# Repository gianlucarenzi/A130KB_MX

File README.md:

# A130KB_MX
ATARI XE Replacement Keyboard

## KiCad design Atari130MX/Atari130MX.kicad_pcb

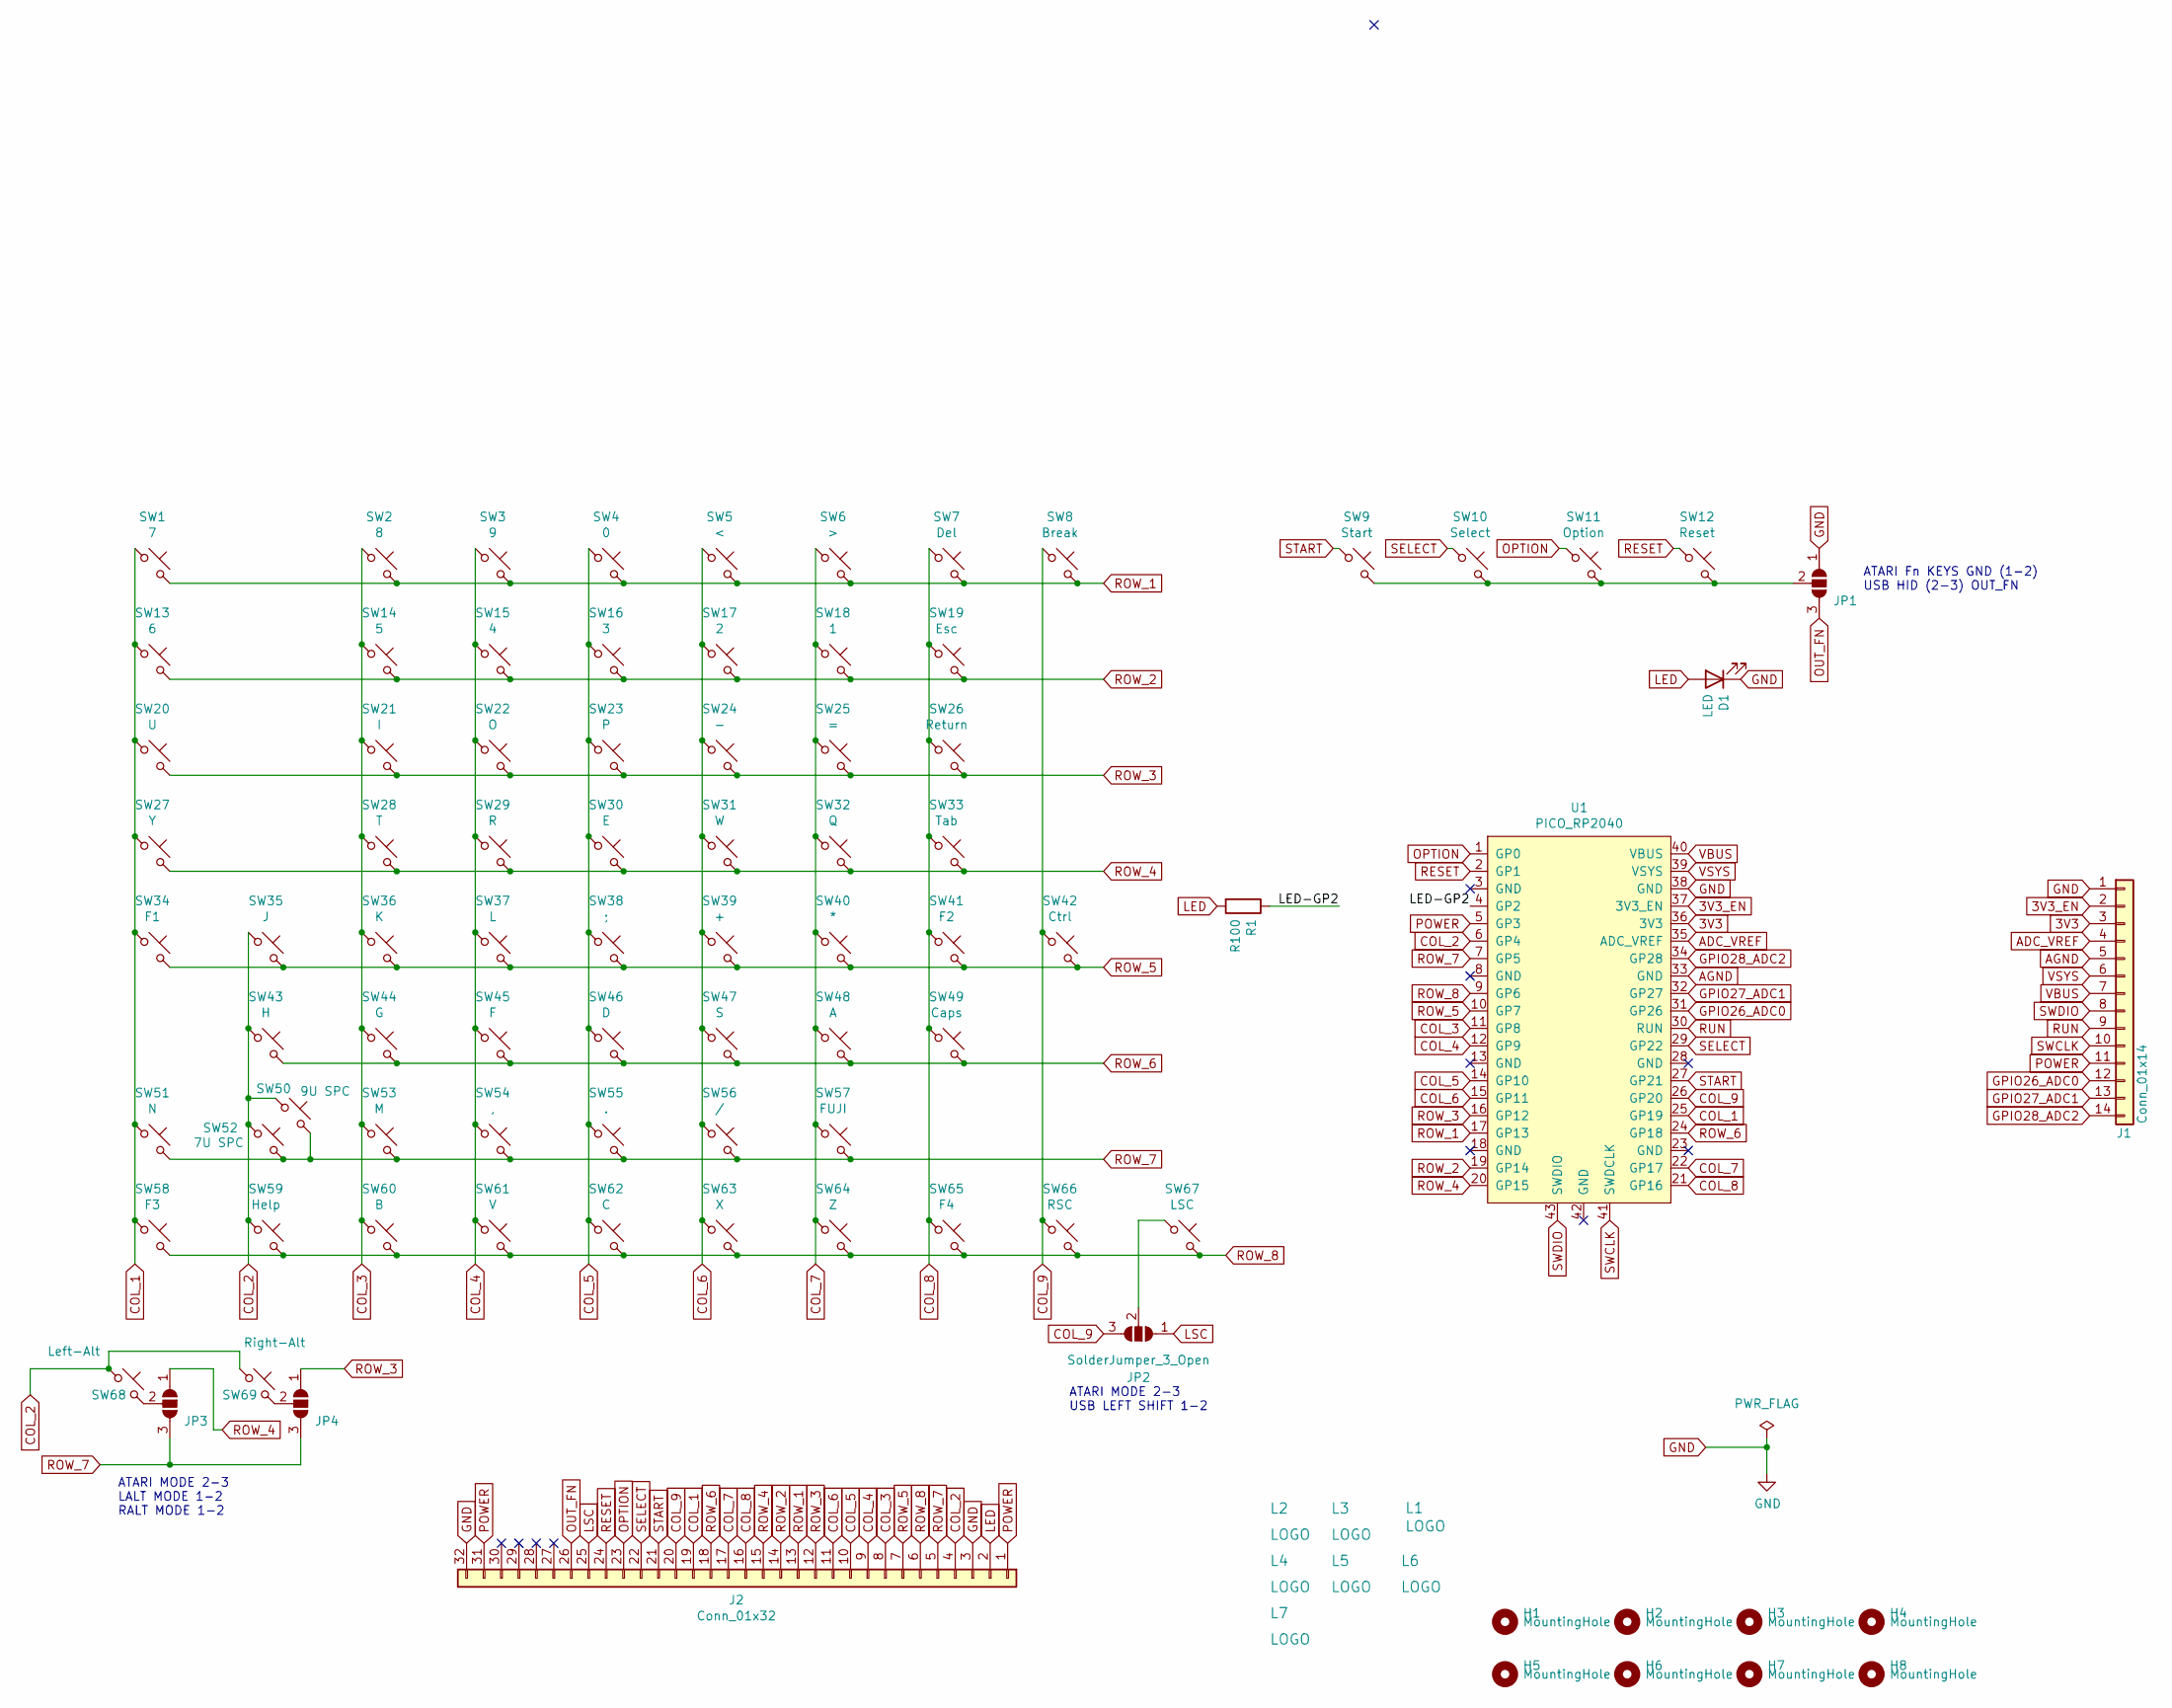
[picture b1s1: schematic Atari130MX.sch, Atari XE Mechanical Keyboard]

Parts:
D1: LED; LED_D3.0mm_Horizontal_O1.27mm_Z2.0mm
H1, H2, H3, H4, H5, H6, H7, H8: MountingHole; MountingHole_3.2mm_M3
J1: Conn_01x14; PinHeader_1x14_P2.54mm_Vertical
J2: Conn_01x32; MOLEX-FFC-1.25mm-RA-52044-3245
JP1, JP2, JP3, JP4: SolderJumper_3_Open; SolderJumper-3_P1.3mm_Open_RoundedPad1.0x1.5mm
L1: LOGO; atari_ready_8mm_rev
L2: LOGO; AtariXE_Matrix
L3, L7: LOGO; OSH_logo
L4: LOGO; Decent_logo
L5, L6: LOGO; ScreamingAtTheRadio
R1: R100; R_Axial_DIN0207_L6.3mm_D2.5mm_P7.62mm_Horizontal
SW1: 7; SW_Kailh_1.00u_PCB_noSwitch
SW2: 8; SW_Kailh_1.00u_PCB_noSwitch
SW3: 9; SW_Kailh_1.00u_PCB_noSwitch
SW4: 0; SW_Kailh_1.00u_PCB_noSwitch
SW5: <; SW_Kailh_1.00u_PCB_noSwitch
SW6: >; SW_Kailh_1.00u_PCB_noSwitch
SW7: Del; SW_Kailh_1.00u_PCB_noSwitch
SW8: Break; SW_Kailh_1.00u_PCB_noSwitch
SW9: Start; SW_Kailh_1.50u_Atari_Fn_PCB_noSwitch
SW10: Select; SW_Kailh_1.50u_Atari_Fn_PCB_noSwitch
SW11: Option; SW_Kailh_1.50u_Atari_Fn_PCB_noSwitch
SW12: Reset; SW_Kailh_1.50u_Atari_Fn_PCB_noSwitch
SW13: 6; SW_Kailh_1.00u_PCB_noSwitch
SW14: 5; SW_Kailh_1.00u_PCB_noSwitch
SW15: 4; SW_Kailh_1.00u_PCB_noSwitch
SW16: 3; SW_Kailh_1.00u_PCB_noSwitch
SW17: 2; SW_Kailh_1.00u_PCB_noSwitch
SW18: 1; SW_Kailh_1.00u_PCB_noSwitch
SW19: Esc; SW_Kailh_1.00u_PCB_noSwitch
SW20: U; SW_Kailh_1.00u_PCB_noSwitch
SW21: I; SW_Kailh_1.00u_PCB_noSwitch
SW22: O; SW_Kailh_1.00u_PCB_noSwitch
SW23: P; SW_Kailh_1.00u_PCB_noSwitch
SW24: -; SW_Kailh_1.00u_PCB_noSwitch
SW25: =; SW_Kailh_1.00u_PCB_noSwitch
SW26: Return; SW_Kailh_1.50u_PCB_noSwitch
SW27: Y; SW_Kailh_1.00u_PCB_noSwitch
SW28: T; SW_Kailh_1.00u_PCB_noSwitch
SW29: R; SW_Kailh_1.00u_PCB_noSwitch
SW30: E; SW_Kailh_1.00u_PCB_noSwitch
SW31: W; SW_Kailh_1.00u_PCB_noSwitch
SW32: Q; SW_Kailh_1.00u_PCB_noSwitch
SW33: Tab; SW_Kailh_1.50u_PCB_noSwitch
SW34: F1; SW_Kailh_1.50u_Atari_Fn_PCB_noSwitch
SW35: J; SW_Kailh_1.00u_PCB_noSwitch
SW36: K; SW_Kailh_1.00u_PCB_noSwitch
SW37: L; SW_Kailh_1.00u_PCB_noSwitch
SW38: ;; SW_Kailh_1.00u_PCB_noSwitch
SW39: +; SW_Kailh_1.00u_PCB_noSwitch
SW40: *; SW_Kailh_1.00u_PCB_noSwitch
SW41: F2; SW_Kailh_1.50u_Atari_Fn_PCB_noSwitch
SW42: Ctrl; SW_Kailh_1.75u_PCB_noSwitch
SW43: H; SW_Kailh_1.00u_PCB_noSwitch
SW44: G; SW_Kailh_1.00u_PCB_noSwitch
SW45: F; SW_Kailh_1.00u_PCB_noSwitch
SW46: D; SW_Kailh_1.00u_PCB_noSwitch
SW47: S; SW_Kailh_1.00u_PCB_noSwitch
SW48: A; SW_Kailh_1.00u_PCB_noSwitch
SW49: Caps; SW_Kailh_1.25u_PCB_noSwitch
SW50: 9U SPC; SW_Cherry_MX1A_9u_PCB_noSwitch
SW51: N; SW_Kailh_1.00u_PCB_noSwitch
SW52: 7U SPC; MXOnly-7U-NoLED
SW53: M; SW_Kailh_1.00u_PCB_noSwitch
SW54: ,; SW_Kailh_1.00u_PCB_noSwitch
SW55: .; SW_Kailh_1.00u_PCB_noSwitch
SW56: /; SW_Kailh_1.00u_PCB_noSwitch
SW57: FUJI; SW_Kailh_1.00u_PCB_noSwitch
SW58: F3; SW_Kailh_1.50u_Atari_Fn_PCB_noSwitch
SW59: Help; SW_Kailh_1.50u_Atari_Fn_PCB_noSwitch
SW60: B; SW_Kailh_1.00u_PCB_noSwitch
SW61: V; SW_Kailh_1.00u_PCB_noSwitch
SW62: C; SW_Kailh_1.00u_PCB_noSwitch
SW63: X; SW_Kailh_1.00u_PCB_noSwitch
SW64: Z; SW_Kailh_1.00u_PCB_noSwitch
SW65: F4; SW_Kailh_1.50u_Atari_Fn_PCB_noSwitch
SW66: RSC; SW_Kailh_1.75u_PCB_noSwitch
SW67: LSC; SW_Kailh_2.25u_PCB_noSwitch
SW68: Left-Alt; SW_Kailh_1.00u_PCB_noSwitch
SW69: Right-Alt; SW_Kailh_1.00u_PCB_noSwitch
U1: PICO_RP2040; RPi_Pico_SMD_TH

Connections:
3V3: J1.3, U1.36 (3V3)
3V3_EN: J1.2, U1.37 (3V3_EN)
/LED-GP2: R1.1, U1.4 (GP2)
ADC_VREF: J1.4, U1.35 (ADC_VREF)
AGND: J1.5, U1.33 (GND)
COL_1: J2.19, SW1.1, SW13.1, SW20.1, SW27.1, SW34.1, SW51.1, SW58.1, U1.25 (GP19)
COL_2: J2.4, SW35.1, SW43.1, SW50.1, SW52.1, SW59.1, SW68.1, SW69.1, U1.6 (GP4)
COL_3: J2.8, SW2.1, SW14.1, SW21.1, SW28.1, SW36.1, SW44.1, SW53.1, SW60.1, U1.11 (GP8)
COL_4: J2.9, SW3.1, SW15.1, SW22.1, SW29.1, SW37.1, SW45.1, SW54.1, SW61.1, U1.12 (GP9)
COL_5: J2.10, SW4.1, SW16.1, SW23.1, SW30.1, SW38.1, SW46.1, SW55.1, SW62.1, U1.14 (GP10)
COL_6: J2.11, SW5.1, SW17.1, SW24.1, SW31.1, SW39.1, SW47.1, SW56.1, SW63.1, U1.15 (GP11)
COL_7: J2.17, SW6.1, SW18.1, SW25.1, SW32.1, SW40.1, SW48.1, SW57.1, SW64.1, U1.22 (GP17)
COL_8: J2.16, SW7.1, SW19.1, SW26.1, SW33.1, SW41.1, SW49.1, SW65.1, U1.21 (GP16)
COL_9: J2.20, JP2.3 (B), SW8.1, SW42.1, SW66.1, U1.26 (GP20)
GND: D1.1 (K), J1.1, J2.3, J2.32, JP1.1 (A), U1.38 (GND)
GPIO26_ADC0: J1.12, U1.31 (GP26)
GPIO27_ADC1: J1.13, U1.32 (GP27)
GPIO28_ADC2: J1.14, U1.34 (GP28)
LED: D1.2 (A), J2.2, R1.2
LSC: J2.25, JP2.1 (A)
unnamed: JP1.2 (C), SW9.2, SW10.2, SW11.2, SW12.2
unnamed: JP2.2 (C), SW67.1
unnamed: JP3.2 (C), SW68.2
unnamed: JP4.2 (C), SW69.2
OPTION: J2.23, SW11.1, U1.1 (GP0)
OUT_FN: J2.26, JP1.3 (B)
POWER: J1.11, J2.1, J2.31, U1.5 (GP3)
RESET: J2.24, SW12.1, U1.2 (GP1)
ROW_1: J2.13, SW1.2, SW2.2, SW3.2, SW4.2, SW5.2, SW6.2, SW7.2, SW8.2, U1.17 (GP13)
ROW_2: J2.14, SW13.2, SW14.2, SW15.2, SW16.2, SW17.2, SW18.2, SW19.2, U1.19 (GP14)
ROW_3: J2.12, JP4.1 (A), SW20.2, SW21.2, SW22.2, SW23.2, SW24.2, SW25.2, SW26.2, U1.16 (GP12)
ROW_4: J2.15, JP3.1 (A), SW27.2, SW28.2, SW29.2, SW30.2, SW31.2, SW32.2, SW33.2, U1.20 (GP15)
ROW_5: J2.7, SW34.2, SW35.2, SW36.2, SW37.2, SW38.2, SW39.2, SW40.2, SW41.2, SW42.2, U1.10 (GP7)
ROW_6: J2.18, SW43.2, SW44.2, SW45.2, SW46.2, SW47.2, SW48.2, SW49.2, U1.24 (GP18)
ROW_7: J2.5, JP3.3 (B), JP4.3 (B), SW50.2, SW51.2, SW52.2, SW53.2, SW54.2, SW55.2, SW56.2, SW57.2, U1.7 (GP5)
ROW_8: J2.6, SW58.2, SW59.2, SW60.2, SW61.2, SW62.2, SW63.2, SW64.2, SW65.2, SW66.2, SW67.2, U1.9 (GP6)
RUN: J1.9, U1.30 (RUN)
SELECT: J2.22, SW10.1, U1.29 (GP22)
START: J2.21, SW9.1, U1.27 (GP21)
SWCLK: J1.10, U1.41 (SWDCLK)
SWDIO: J1.8, U1.43 (SWDIO)
VBUS: J1.7, U1.40 (VBUS)
VSYS: J1.6, U1.39 (VSYS)

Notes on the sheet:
ATARI MODE 2-3 USB LEFT SHIFT 1-2
ATARI MODE 2-3 LALT MODE 1-2 RALT MODE 1-2
ATARI Fn KEYS GND (1-2) USB HID (2-3) OUT_FN

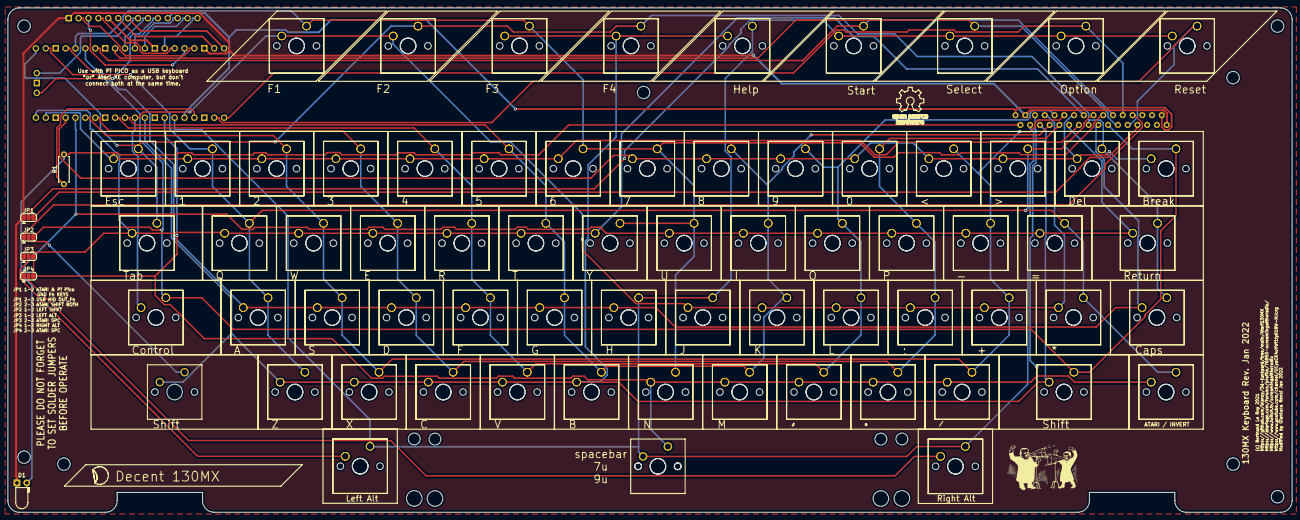
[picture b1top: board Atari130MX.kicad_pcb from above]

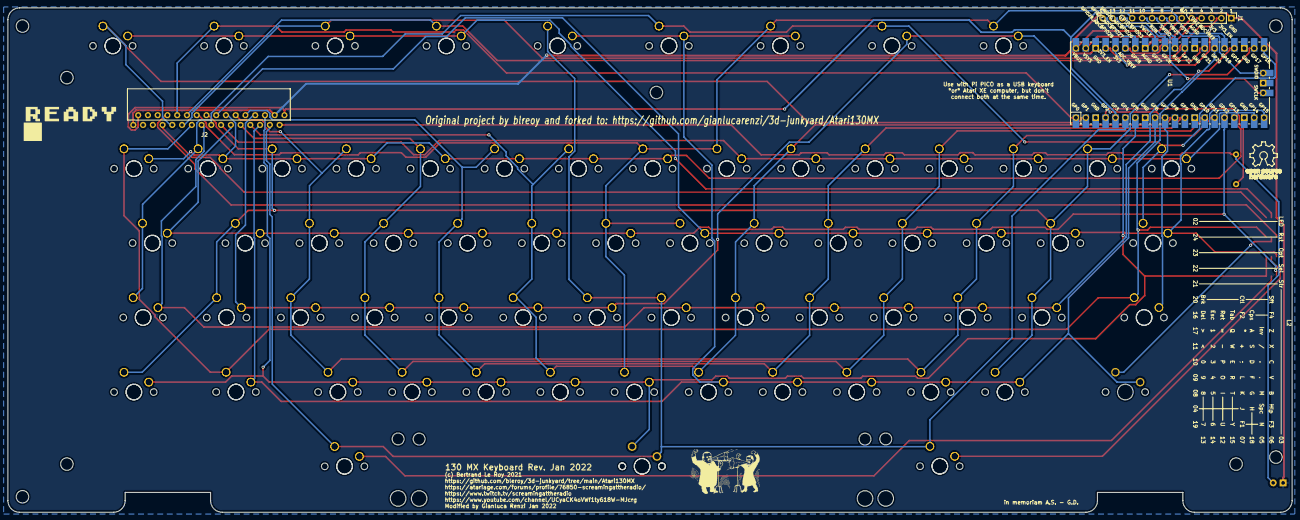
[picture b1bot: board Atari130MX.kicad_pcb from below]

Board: 2 copper layers, 329.2 x 129.3 mm, 93 parts (7 on the bottom side), 43 nets.

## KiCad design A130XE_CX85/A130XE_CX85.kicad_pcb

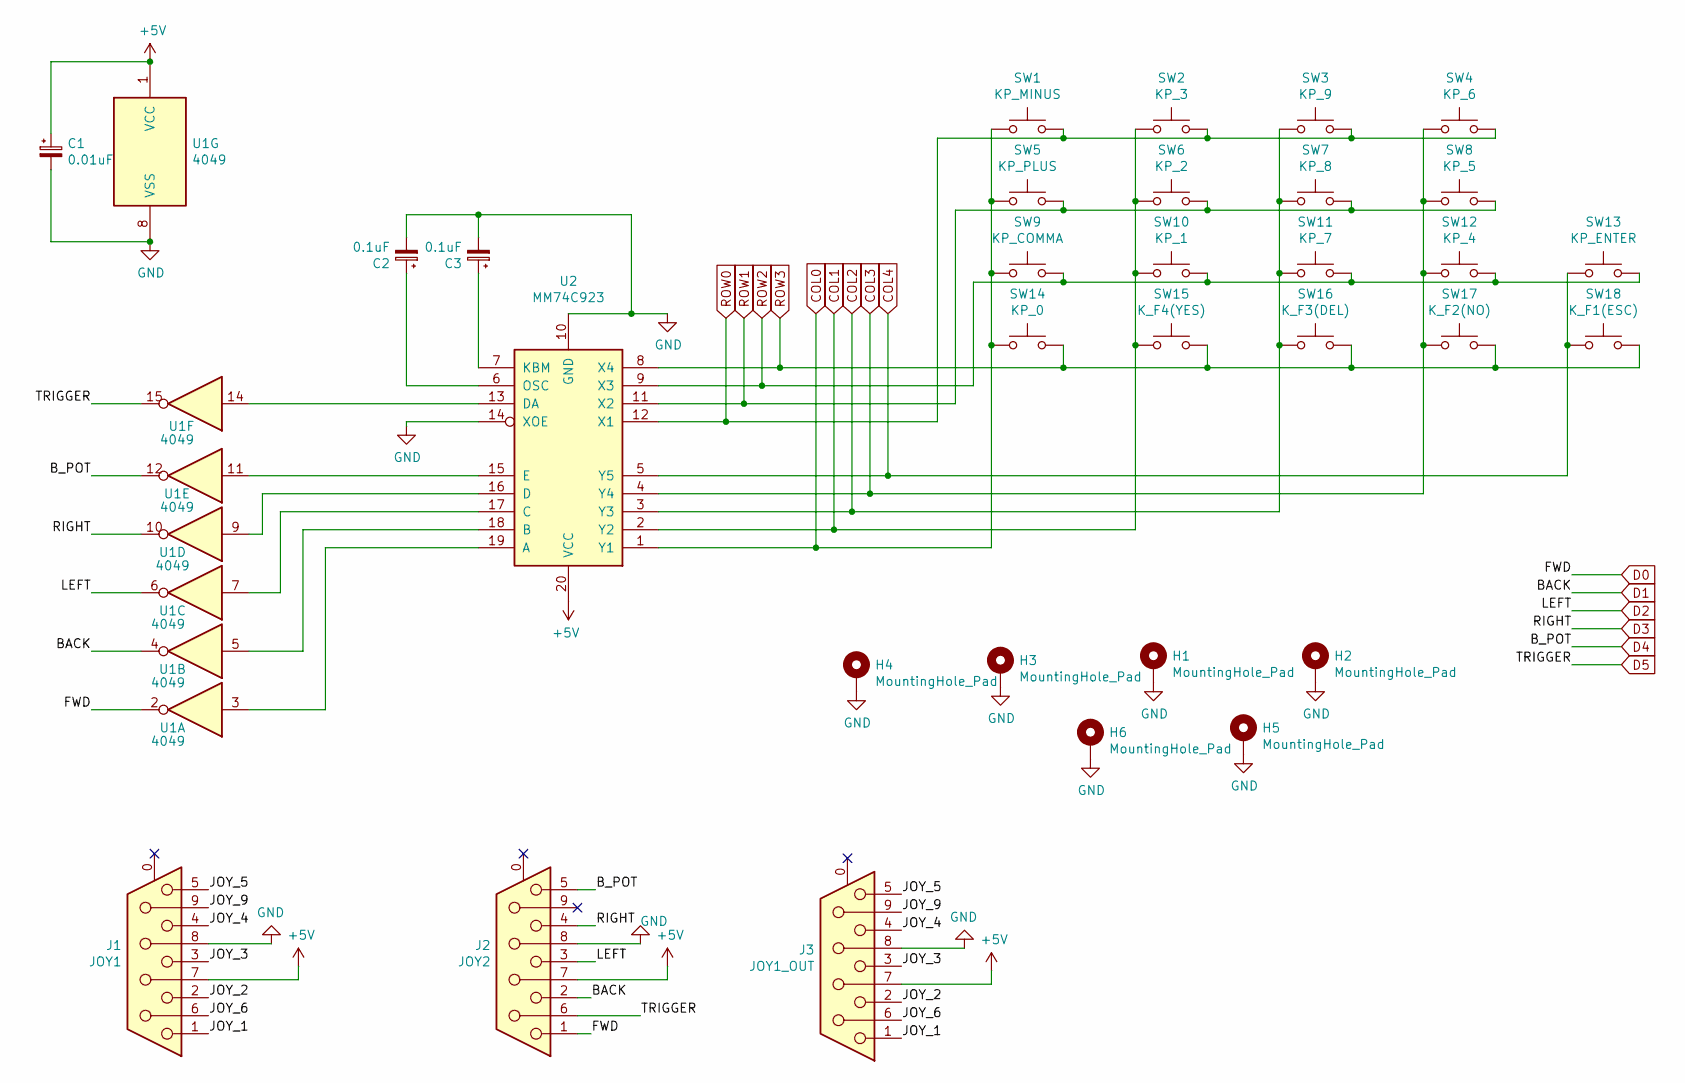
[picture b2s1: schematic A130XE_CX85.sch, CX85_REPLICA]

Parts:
C1: 0.01uF; C_Disc_D5.0mm_W2.5mm_P2.50mm
C2, C3: 0.1uF; C_Disc_D5.0mm_W2.5mm_P2.50mm
H1, H2, H3, H4, H5, H6: MountingHole_Pad; MountingHole_3.2mm_M3_DIN965_Pad
J1: JOY1; DSUB-9_Female_Horizontal_P2.77x2.54mm_EdgePinOffset9.40mm
J2: JOY2; DSUB-9_Female_Horizontal_P2.77x2.54mm_EdgePinOffset9.40mm
J3: JOY1_OUT; DSUB-9_Male_Horizontal_P2.77x2.54mm_EdgePinOffset9.40mm
SW1: KP_MINUS; SW_Cherry_MX_1.00u_PCB
SW2: KP_3; SW_Cherry_MX_1.00u_PCB
SW3: KP_9; SW_Cherry_MX_1.00u_PCB
SW4: KP_6; SW_Cherry_MX_1.00u_PCB
SW5: KP_PLUS; SW_Cherry_MX_1.00u_PCB
SW6: KP_2; SW_Cherry_MX_1.00u_PCB
SW7: KP_8; SW_Cherry_MX_1.00u_PCB
SW8: KP_5; SW_Cherry_MX_1.00u_PCB
SW9: KP_COMMA; SW_Cherry_MX_1.00u_PCB
SW10: KP_1; SW_Cherry_MX_1.00u_PCB
SW11: KP_7; SW_Cherry_MX_1.00u_PCB
SW12: KP_4; SW_Cherry_MX_1.00u_PCB
SW13: KP_ENTER; SW_Cherry_MX_2.00u_Vertical_PCB
SW14: KP_0; SW_Cherry_MX_2.00u_PCB
SW15: K_F4(YES); SW_Cherry_MX_1.00u_PCB
SW16: K_F3(DEL); SW_Cherry_MX_1.00u_PCB
SW17: K_F2(NO); SW_Cherry_MX_1.00u_PCB
SW18: K_F1(ESC); SW_Cherry_MX_1.00u_PCB
U1: 4049; DIP-16_W7.62mm
U2: MM74C923; DIP-20_W7.62mm

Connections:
+5V: C1.1, J1.7, J2.7, J3.7, U1.1 (VCC), U2.20 (VCC)
/JOY_1: J1.1, J3.1
/JOY_2: J1.2, J3.2
/JOY_3: J1.3, J3.3
/JOY_4: J1.4, J3.4
/JOY_5: J1.5, J3.5
/JOY_6: J1.6, J3.6
/JOY_9: J1.9, J3.9
COL0: SW1.1, SW5.1, SW9.1, SW14.1, U2.1 (Y1)
COL1: SW2.1, SW6.1, SW10.1, SW15.1, U2.2 (Y2)
COL2: SW3.1, SW7.1, SW11.1, SW16.1, U2.3 (Y3)
COL3: SW4.1, SW8.1, SW12.1, SW17.1, U2.4 (Y4)
COL4: SW13.1, SW18.1, U2.5 (Y5)
D0: J2.1, U1.2
D1: J2.2, U1.4
D2: J2.3, U1.6
D3: J2.4, U1.10
D4: J2.5, U1.12
D5: J2.6, U1.15
GND: C1.2, C2.2, C3.2, H1.1, H2.1, H3.1, H4.1, H5.1, H6.1, J1.8, J2.8, J3.8, U1.8 (VSS), U2.10 (GND), U2.14 (XOE)
unnamed: C2.1, U2.6 (OSC)
unnamed: C3.1, U2.7 (KBM)
unnamed: U1.3, U2.19 (A)
unnamed: U1.5, U2.18 (B)
unnamed: U1.7, U2.17 (C)
unnamed: U1.9, U2.16 (D)
unnamed: U1.11, U2.15 (E)
unnamed: U1.14, U2.13 (DA)
ROW0: SW1.2, SW2.2, SW3.2, SW4.2, U2.12 (X1)
ROW1: SW5.2, SW6.2, SW7.2, SW8.2, U2.11 (X2)
ROW2: SW9.2, SW10.2, SW11.2, SW12.2, SW13.2, U2.9 (X3)
ROW3: SW14.2, SW15.2, SW16.2, SW17.2, SW18.2, U2.8 (X4)

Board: 2 copper layers, 32 parts (0 on the bottom side), 32 nets, no tracks yet.

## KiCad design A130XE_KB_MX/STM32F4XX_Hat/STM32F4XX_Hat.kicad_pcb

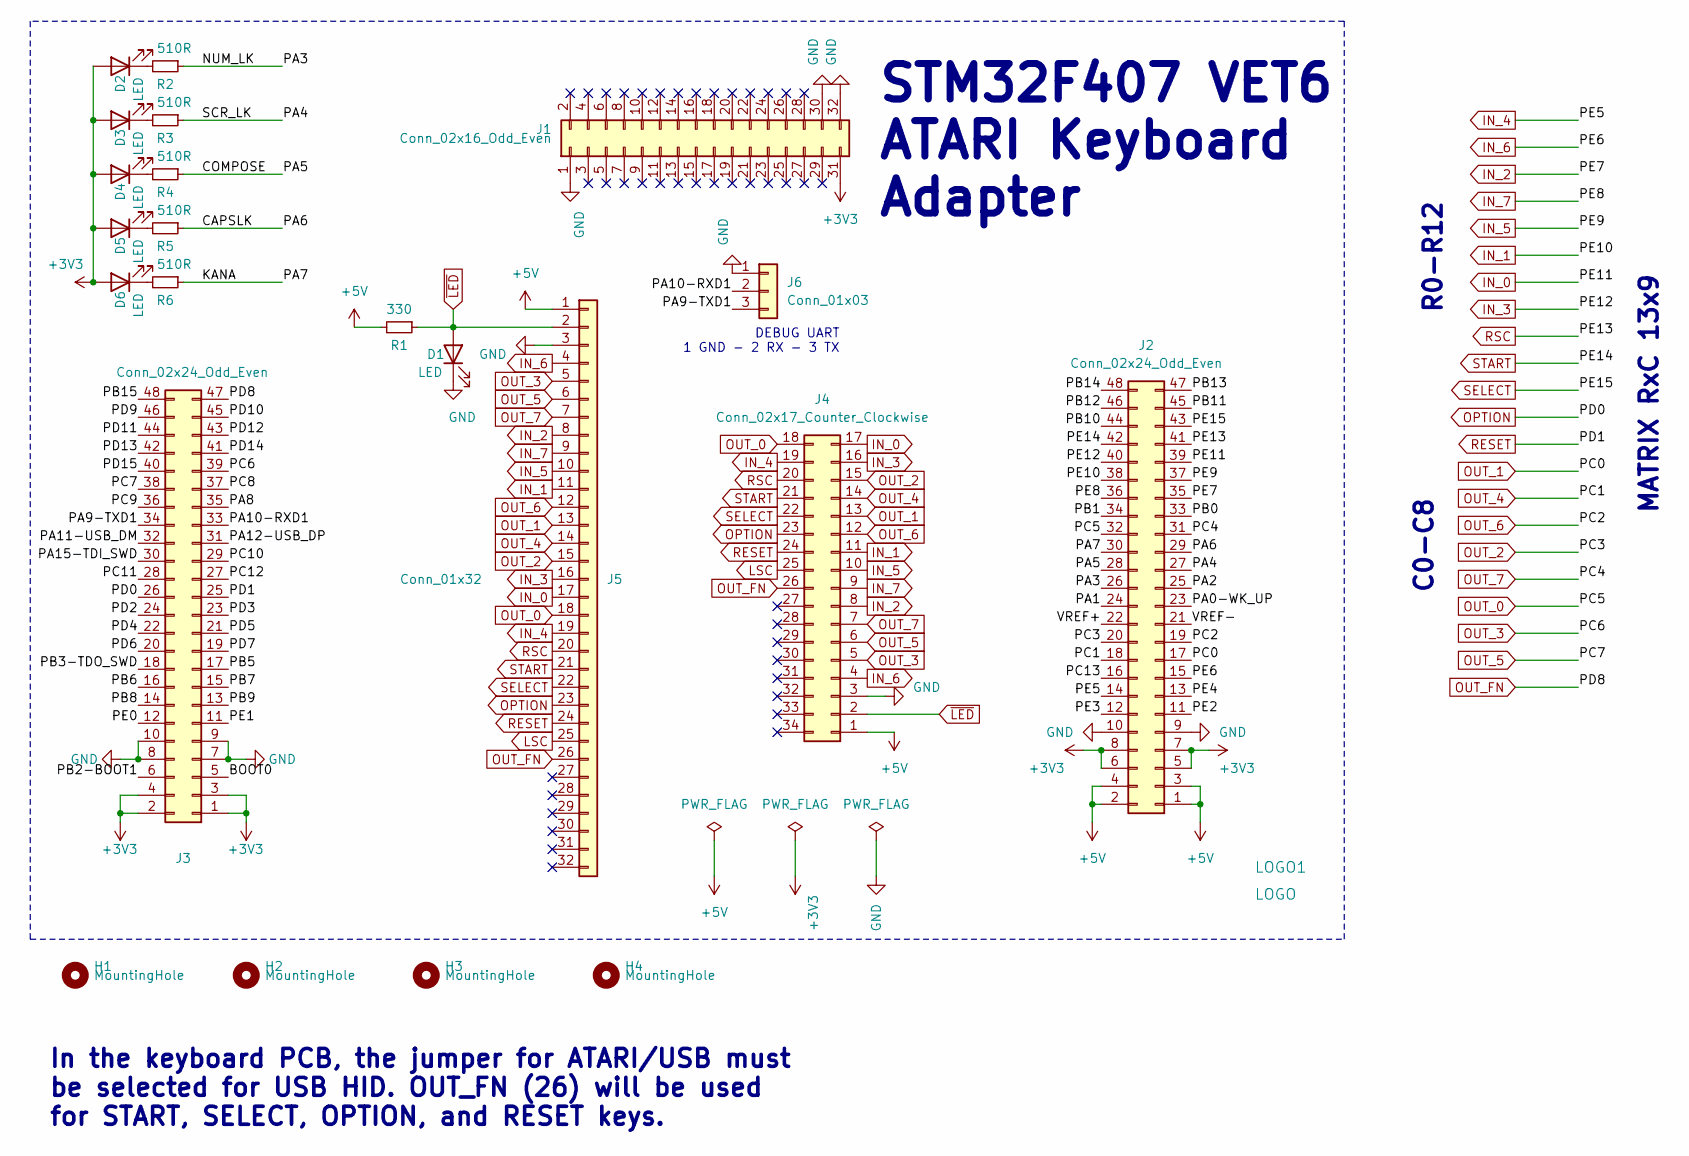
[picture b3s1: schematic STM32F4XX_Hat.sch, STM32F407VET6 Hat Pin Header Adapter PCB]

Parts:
D1, D2, D3, D4, D5, D6: LED; LED_D5.0mm
H1, H2, H3, H4: MountingHole; MountingHole_3.5mm
J1: Conn_02x16_Odd_Even; PinSocket_2x16_P2.54mm_Vertical
J2, J3: Conn_02x24_Odd_Even; PinSocket_2x24_P2.54mm_Vertical
J4: Conn_02x17_Counter_Clockwise; IDC-Header_2x17_P2.54mm_Vertical
J5: Conn_01x32; MOLEX-FFC-1.25mm-RA-52044-3245
J6: Conn_01x03; PinHeader_1x03_P2.54mm_Vertical
LOGO1: LOGO; atari_ready_8mm_rev
R1: 330; R_Axial_DIN0204_L3.6mm_D1.6mm_P2.54mm_Vertical
R2, R3, R4, R5, R6: 510R; R_Axial_DIN0204_L3.6mm_D1.6mm_P2.54mm_Vertical

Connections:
+3V3: D2.2 (A), D3.2 (A), D4.2 (A), D5.2 (A), D6.2 (A), J1.31, J2.5, J2.6, J2.7, J2.8, J3.1, J3.2, J3.3, J3.4
+5V: J2.1, J2.2, J2.3, J2.4, J4.1, J5.1, R1.2
/BOOT0: J3.5
/CAPSLK: J2.29, R5.1
/COMPOSE: J2.28, R4.1
/KANA: J2.30, R6.1
/NUM_LK: J2.26, R2.1
/PA0-WK_UP: J2.23
/PA1: J2.24
/PA2: J2.25
/PA4: J2.27, R3.1
/PA8: J3.35
/PA9-TXD1: J3.34, J6.3
/PA10-RXD1: J3.33, J6.2
/PA11-USB_DM: J3.32
/PA12-USB_DP: J3.31
/PA15-TDI_SWD: J3.30
/PB0: J2.33
/PB1: J2.34
/PB2-BOOT1: J3.6
/PB3-TDO_SWD: J3.18
/PB5: J3.17
/PB6: J3.16
/PB7: J3.15
/PB8: J3.14
/PB9: J3.13
/PB10: J2.44
/PB11: J2.45
/PB12: J2.46
/PB13: J2.47
/PB14: J2.48
/PB15: J3.48
/PC8: J3.37
/PC9: J3.36
/PC10: J3.29
/PC11: J3.28
/PC12: J3.27
/PC13: J2.16
/PD2: J3.24
/PD3: J3.23
/PD4: J3.22
/PD5: J3.21
/PD6: J3.20
/PD7: J3.19
/PD9: J3.46
/PD10: J3.45
/PD11: J3.44
/PD12: J3.43
/PD13: J3.42
/PD14: J3.41
/PD15: J3.40
/PE0: J3.12
/PE1: J3.11
/PE2: J2.11
/PE3: J2.12
/PE4: J2.13
/VREF+: J2.22
/VREF-: J2.21
GND: D1.1 (K), J1.1, J1.30, J1.32, J2.9, J2.10, J3.7, J3.8, J3.9, J3.10, J4.3, J5.3, J6.1
IN_0: J2.39, J4.17, J5.17
IN_1: J2.38, J4.11, J5.11
IN_2: J2.35, J4.8, J5.8
IN_3: J2.40, J4.16, J5.16
IN_4: J2.14, J4.19, J5.19
IN_5: J2.37, J4.10, J5.10
IN_6: J2.15, J4.4, J5.4
IN_7: J2.36, J4.9, J5.9
LSC: J4.25, J5.25
unnamed: D2.1 (K), R2.2
unnamed: D3.1 (K), R3.2
unnamed: D4.1 (K), R4.2
unnamed: D5.1 (K), R5.2
unnamed: D6.1 (K), R6.2
OPTION: J3.26, J4.23, J5.23
OUT_0: J2.32, J4.18, J5.18
OUT_1: J2.17, J4.13, J5.13
OUT_2: J2.20, J4.15, J5.15
OUT_3: J3.39, J4.5, J5.5
OUT_4: J2.18, J4.14, J5.14
OUT_5: J3.38, J4.6, J5.6
OUT_6: J2.19, J4.12, J5.12
OUT_7: J2.31, J4.7, J5.7
OUT_FN: J3.47, J4.26, J5.26
RESET: J3.25, J4.24, J5.24
RSC: J2.41, J4.20, J5.20
SELECT: J2.43, J4.22, J5.22
START: J2.42, J4.21, J5.21
~LED: D1.2 (A), J4.2, J5.2, R1.1

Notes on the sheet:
STM32F407 VET6 ATARI Keyboard Adapter
In the keyboard PCB, the jumper for ATARI/USB must be selected for USB HID. OUT_FN (26) will be used for START, SELECT, OPTION, and RESET keys.
R0-R12
C0-C8
MATRIX RxC 13x9
DEBUG UART 1 GND - 2 RX - 3 TX

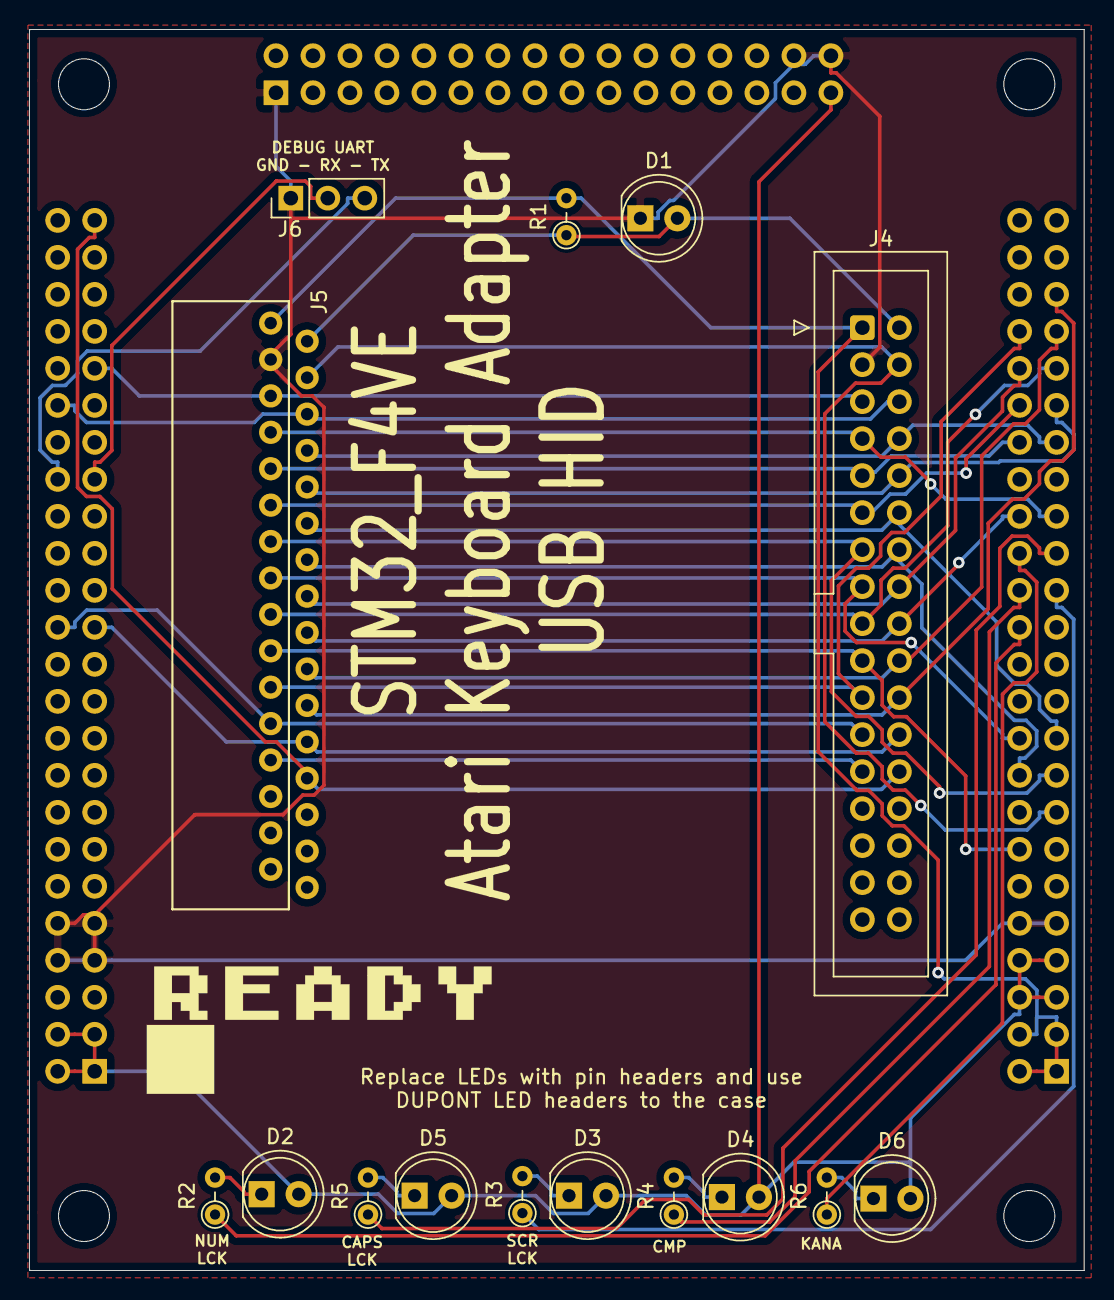
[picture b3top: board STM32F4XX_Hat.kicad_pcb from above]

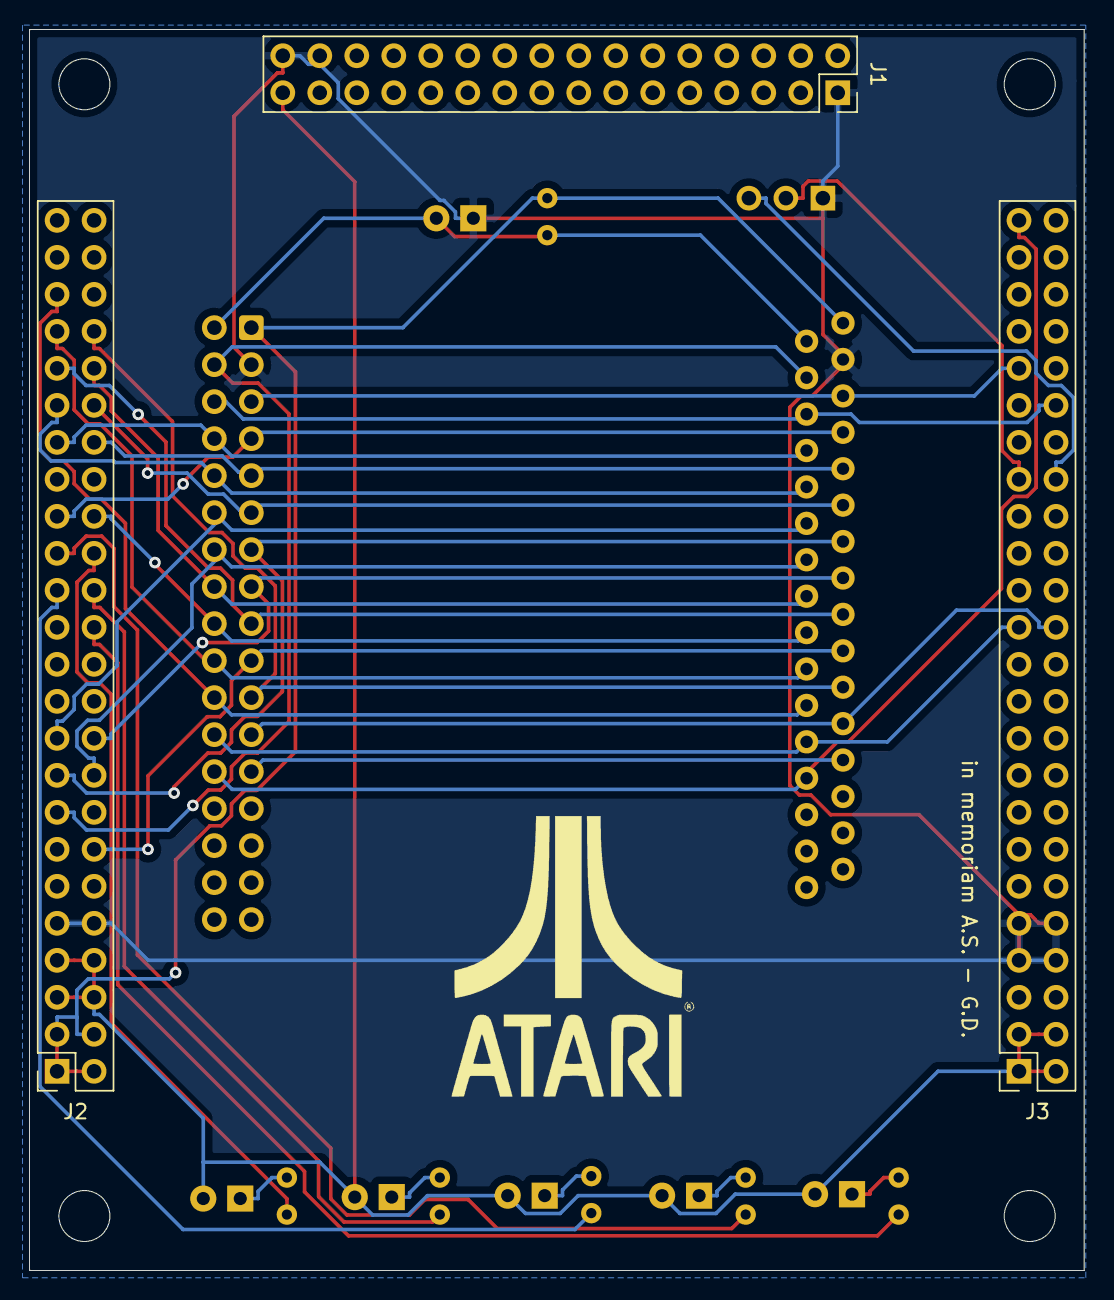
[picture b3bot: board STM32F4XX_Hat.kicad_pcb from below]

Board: 2 copper layers, 72.4 x 85.2 mm, 23 parts (3 on the bottom side), 39 nets.

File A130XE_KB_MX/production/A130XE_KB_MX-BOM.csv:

"Id";"Designator";"Package";"Quantity";"Designation";"Supplier and ref";
1;"H1,H2,H3,H4";"MountingHole_3.7mm";4;"MountingHole";;;
2;"SW67";"SW_Cherry_MX1A_1.00u_PCB_3d";1;"K_F3";;;
3;"SW47";"SW_Cherry_MX1A_1.00u_PCB_3d";1;"K_ATARI";;;
4;"SW55";"SW_Cherry_MX1A_1.00u_PCB_3d";1;"K_BRK";;;
5;"SW56";"SW_Cherry_MX1A_1.00u_PCB_3d";1;"K_DEL";;;
6;"SW57";"SW_Cherry_MX1A_1.00u_PCB_3d";1;"K_GT";;;
7;"SW58";"SW_Cherry_MX1A_1.00u_PCB_3d";1;"K_LT";;;
8;"SW59";"SW_Cherry_MX1A_1.00u_PCB_3d";1;"K_0";;;
9;"SW60";"SW_Cherry_MX1A_1.00u_PCB_3d";1;"K_9";;;
10;"SW61";"SW_Cherry_MX1A_1.00u_PCB_3d";1;"K_8";;;
11;"SW62";"SW_Cherry_MX1A_1.00u_PCB_3d";1;"K_7";;;
12;"SW66";"SW_Cherry_MX1A_1.00u_PCB_3d";1;"K_F2";;;
13;"SW33";"SW_Cherry_MX1A_1.00u_PCB_3d";1;"K_dot";;;
14;"SW48";"SW_Cherry_MX1A_1.00u_PCB_3d";1;"K_ESC";;;
15;"SW31";"SW_Cherry_MX1A_1.00u_PCB_3d";1;"K_comdot";;;
16;"SW36";"SW_Cherry_MX1A_1.00u_PCB_3d";1;"K_W";;;
17;"SW37";"SW_Cherry_MX1A_1.00u_PCB_3d";1;"K_S";;;
18;"SW38";"SW_Cherry_MX1A_1.00u_PCB_3d";1;"K_X";;;
19;"SW39";"SW_Cherry_MX1A_1.00u_PCB_3d";1;"K_plus";;;
20;"SW40";"SW_Cherry_MX1A_1.00u_PCB_3d";1;"K_1";;;
21;"SW41";"SW_Cherry_MX1A_1.00u_PCB_3d";1;"K_equal";;;
22;"SW42";"SW_Cherry_MX1A_1.00u_PCB_3d";1;"K_Q";;;
23;"SW43";"SW_Cherry_MX1A_1.00u_PCB_3d";1;"K_A";;;
24;"SW44";"SW_Cherry_MX1A_1.00u_PCB_3d";1;"K_slash";;;
25;"SW35";"SW_Cherry_MX1A_1.00u_PCB_3d";1;"K_minus";;;
26;"SW46";"SW_Cherry_MX1A_1.00u_PCB_3d";1;"K_Z";;;
27;"SW45";"SW_Cherry_MX1A_1.00u_PCB_3d";1;"K_asterisk";;;
28;"SW68";"SW_Cherry_MX1A_1.00u_PCB_3d";1;"K_F4";;;
29;"SW19";"SW_Cherry_MX1A_1.00u_PCB_3d";1;"K_O";;;
30;"SW21";"SW_Cherry_MX1A_1.00u_PCB_3d";1;"K_F";;;
31;"SW22";"SW_Cherry_MX1A_1.00u_PCB_3d";1;"K_M";;;
32;"SW23";"SW_Cherry_MX1A_1.00u_PCB_3d";1;"K_V";;;
33;"SW24";"SW_Cherry_MX1A_1.00u_PCB_3d";1;"K_L";;;
34;"SW25";"SW_Cherry_MX1A_1.00u_PCB_3d";1;"K_3";;;
35;"SW26";"SW_Cherry_MX1A_1.00u_PCB_3d";1;"K_P";;;
36;"SW27";"SW_Cherry_MX1A_1.00u_PCB_3d";1;"K_E";;;
37;"SW28";"SW_Cherry_MX1A_1.00u_PCB_3d";1;"K_D";;;
38;"SW30";"SW_Cherry_MX1A_1.00u_PCB_3d";1;"K_comma";;;
39;"SW32";"SW_Cherry_MX1A_1.00u_PCB_3d";1;"K_C";;;
40;"SW34";"SW_Cherry_MX1A_1.00u_PCB_3d";1;"K_2";;;
41;"SW20";"SW_Cherry_MX1A_1.00u_PCB_3d";1;"K_R";;;
42;"SW18";"SW_Cherry_MX1A_1.00u_PCB_3d";1;"K_4";;;
43;"SW16";"SW_Cherry_MX1A_1.00u_PCB_3d";1;"K_K";;;
44;"SW15";"SW_Cherry_MX1A_1.00u_PCB_3d";1;"K_B";;;
45;"SW13";"SW_Cherry_MX1A_1.00u_PCB_3d";1;"K_G";;;
46;"SW12";"SW_Cherry_MX1A_1.00u_PCB_3d";1;"K_T";;;
47;"SW11";"SW_Cherry_MX1A_1.00u_PCB_3d";1;"K_I";;;
48;"SW10";"SW_Cherry_MX1A_1.00u_PCB_3d";1;"K_5";;;
49;"SW8";"SW_Cherry_MX1A_1.00u_PCB_3d";1;"K_J";;;
50;"SW6";"SW_Cherry_MX1A_1.00u_PCB_3d";1;"K_N";;;
51;"SW5";"SW_Cherry_MX1A_1.00u_PCB_3d";1;"K_H";;;
52;"SW4";"SW_Cherry_MX1A_1.00u_PCB_3d";1;"K_Y";;;
53;"SW3";"SW_Cherry_MX1A_1.00u_PCB_3d";1;"K_U";;;
54;"SW65";"SW_Cherry_MX1A_1.00u_PCB_3d";1;"K_F1";;;
55;"SW2";"SW_Cherry_MX1A_1.00u_PCB_3d";1;"K_6";;;
56;"SW63";"SW_Cherry_MX1A_1.25u_PCB_3d";1;"K_SPACE_1";;;
57;"SW51";"SW_Cherry_MX1A_1.25u_PCB_3d";1;"K_CAPS";;;
58;"SW9";"SW_Cherry_MX1A_1.50u_PCB_3d";1;"KS_OPTION";;;
59;"SW7";"SW_Cherry_MX1A_1.50u_PCB_3d";1;"KS_HELP";;;
60;"SW29";"SW_Cherry_MX1A_1.50u_PCB_3d";1;"KS_START";;;
61;"SW1";"SW_Cherry_MX1A_1.50u_PCB_3d";1;"KS_RESET";;;
62;"SW17";"SW_Cherry_MX1A_1.50u_PCB_3d";1;"KS_SELECT";;;
63;"SW50";"SW_Cherry_MX1A_1.50u_PCB_3d";1;"K_TAB";;;
64;"SW49";"SW_Cherry_MX1A_1.50u_PCB_3d";1;"K_RETURN";;;
65;"SW54";"SW_Cherry_MX1A_1.75u_PCB_3d";1;"K_RSHIFT";;;
66;"SW52";"SW_Cherry_MX1A_1.75u_PCB_3d";1;"K_CTRL";;;
67;"SW53";"SW_Cherry_MX1A_2.25u_PCB_3d";1;"K_LSHIFT";;;
68;"SW14";"SW_Cherry_MX1A_6.25u_PCB_3d";1;"K_SPACE";;;
69;"D1";"LED_1210_3225Metric_Pad1.42x2.65mm_HandSolder";1;"LED_Small";;;
70;"J2";"PinHeader_1x02_P2.54mm_Vertical";1;"Conn_01x02_Male";;;
71;"READY";"atari_ready_14mm_rev";1;"LOGO";;;
72;"SW64";"SW_Cherry_MX1A_1.50u_PCB_3d";1;"K_SPACE_2";;;
73;"J3,J4";"PinHeader_1x03_P2.54mm_Vertical";2;"Conn_01x03_Male";;;
74;"J1";"FFC-1.25mm-RA-5204403245";1;"Conn_01x32";;;
75;"J5";"IDC-Header_2x17_P2.54mm_Vertical";1;"34 pin ribbon keyboard cable";;;

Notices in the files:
A130XE_KB_MX/A130XE_KB_MX.kicad_pcb:
GPL3 License. OPENSOURCE PROJECT
